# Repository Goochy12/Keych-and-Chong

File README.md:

# Keych and Chong
 Keyboard Designs

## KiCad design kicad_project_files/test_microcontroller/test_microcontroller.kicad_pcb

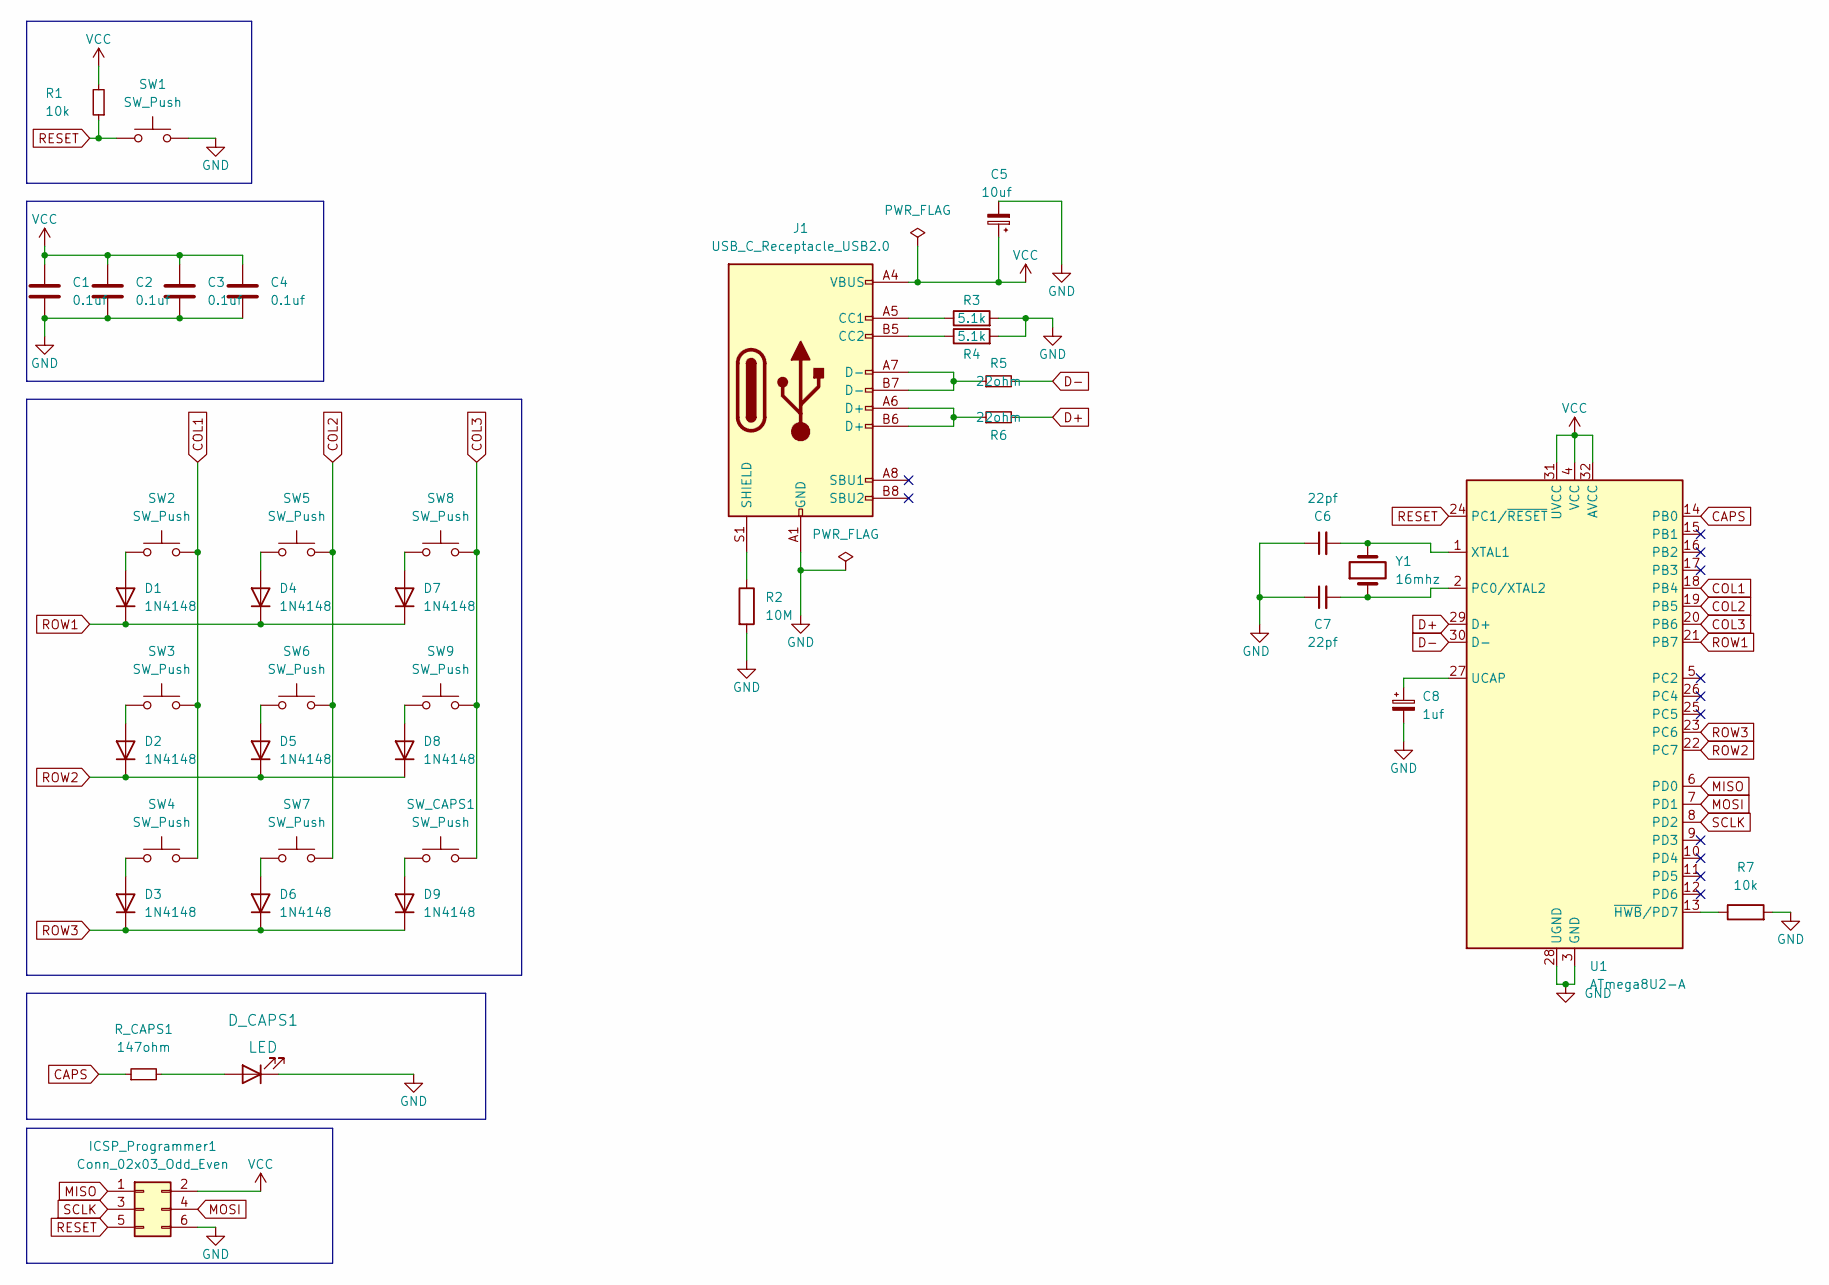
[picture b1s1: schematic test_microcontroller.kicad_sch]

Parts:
C1, C2, C3, C4: 0.1uf; C_Rect_L7.0mm_W2.0mm_P5.00mm
C5: 10uf; CP_Radial_D4.0mm_P1.50mm
C6, C7: 22pf; C_Disc_D3.0mm_W1.6mm_P2.50mm
C8: 1uf; CP_Radial_D4.0mm_P1.50mm
D1, D2, D3, D4, D5, D6, D7, D8, D9: 1N4148; D_DO-35_SOD27_P7.62mm_Horizontal
D_CAPS1: LED; LED_D3.0mm
ICSP_Programmer1: Conn_02x03_Odd_Even; PinHeader_2x03_P2.54mm_Vertical
J1: USB_C_Receptacle_USB2.0; USB_C_Receptacle_HRO_TYPE-C-31-M-12
R1, R7: 10k; R_Axial_DIN0204_L3.6mm_D1.6mm_P7.62mm_Horizontal
R2: 10M; R_Axial_DIN0204_L3.6mm_D1.6mm_P7.62mm_Horizontal
R3, R4: 5.1k; R_Axial_DIN0204_L3.6mm_D1.6mm_P7.62mm_Horizontal
R5, R6: 22ohm; R_Axial_DIN0204_L3.6mm_D1.6mm_P7.62mm_Horizontal
R_CAPS1: 147ohm; R_Axial_DIN0204_L3.6mm_D1.6mm_P7.62mm_Horizontal
SW1, SW2, SW3, SW4, SW5, SW6, SW7, SW8, SW9: SW_Push; SW_4-1437565-0
SW_CAPS1: SW_Push; SW_4-1437565-0
U1: ATmega8U2-A; TQFP-32_7x7mm_P0.8mm
Y1: 16mhz; Crystal_SMD_HC49-SD_HandSoldering

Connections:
CAPS: R_CAPS1.1, U1.14 (PB0)
COL1: SW2.2, SW3.2, SW4.2, U1.18 (PB4)
COL2: SW5.2, SW6.2, SW7.2, U1.19 (PB5)
COL3: SW8.2, SW9.2, SW_CAPS1.2, U1.20 (PB6)
D+: R6.2, U1.29 (D+)
D-: R5.2, U1.30 (D-)
GND: C1.2, C2.2, C3.2, C4.2, C5.2, C6.1, C7.1, C8.2, D_CAPS1.1 (K), ICSP_Programmer1.6, J1.A1 (GND), J1.A12 (GND), J1.B1 (GND), J1.B12 (GND), R2.2, R3.2, R4.2, R7.2, SW1.2, U1.3 (GND), U1.28 (UGND)
MISO: ICSP_Programmer1.1, U1.6 (PD0)
MOSI: ICSP_Programmer1.4, U1.7 (PD1)
unnamed: C6.2, U1.1 (XTAL1), Y1.2
unnamed: C7.2, U1.2 (PC0/XTAL2), Y1.1
unnamed: C8.1, U1.27 (UCAP)
unnamed: D1.2 (A), SW2.1
unnamed: D2.2 (A), SW3.1
unnamed: D3.2 (A), SW4.1
unnamed: D4.2 (A), SW5.1
unnamed: D5.2 (A), SW6.1
unnamed: D6.2 (A), SW7.1
unnamed: D7.2 (A), SW8.1
unnamed: D8.2 (A), SW9.1
unnamed: D9.2 (A), SW_CAPS1.1
unnamed: J1.A5 (CC1), R3.1
unnamed: J1.A6 (D+), J1.B6 (D+), R6.1
unnamed: J1.A7 (D-), J1.B7 (D-), R5.1
unnamed: J1.B5 (CC2), R4.1
unnamed: J1.S1 (SHIELD), R2.1
unnamed: R7.1, U1.13 (~HWB/PD7)
unnamed: D_CAPS1.2 (A), R_CAPS1.2
RESET: ICSP_Programmer1.5, R1.1, SW1.1, U1.24 (PC1/~RESET)
ROW1: D1.1 (K), D4.1 (K), D7.1 (K), U1.21 (PB7)
ROW2: D2.1 (K), D5.1 (K), D8.1 (K), U1.22 (PC7)
ROW3: D3.1 (K), D6.1 (K), D9.1 (K), U1.23 (PC6)
SCLK: ICSP_Programmer1.3, U1.8 (PD2)
VCC: C1.1, C2.1, C3.1, C4.1, C5.1, ICSP_Programmer1.2, J1.A4 (VBUS), J1.A9 (VBUS), J1.B4 (VBUS), J1.B9 (VBUS), R1.2, U1.4 (VCC), U1.31 (UVCC), U1.32 (AVCC)

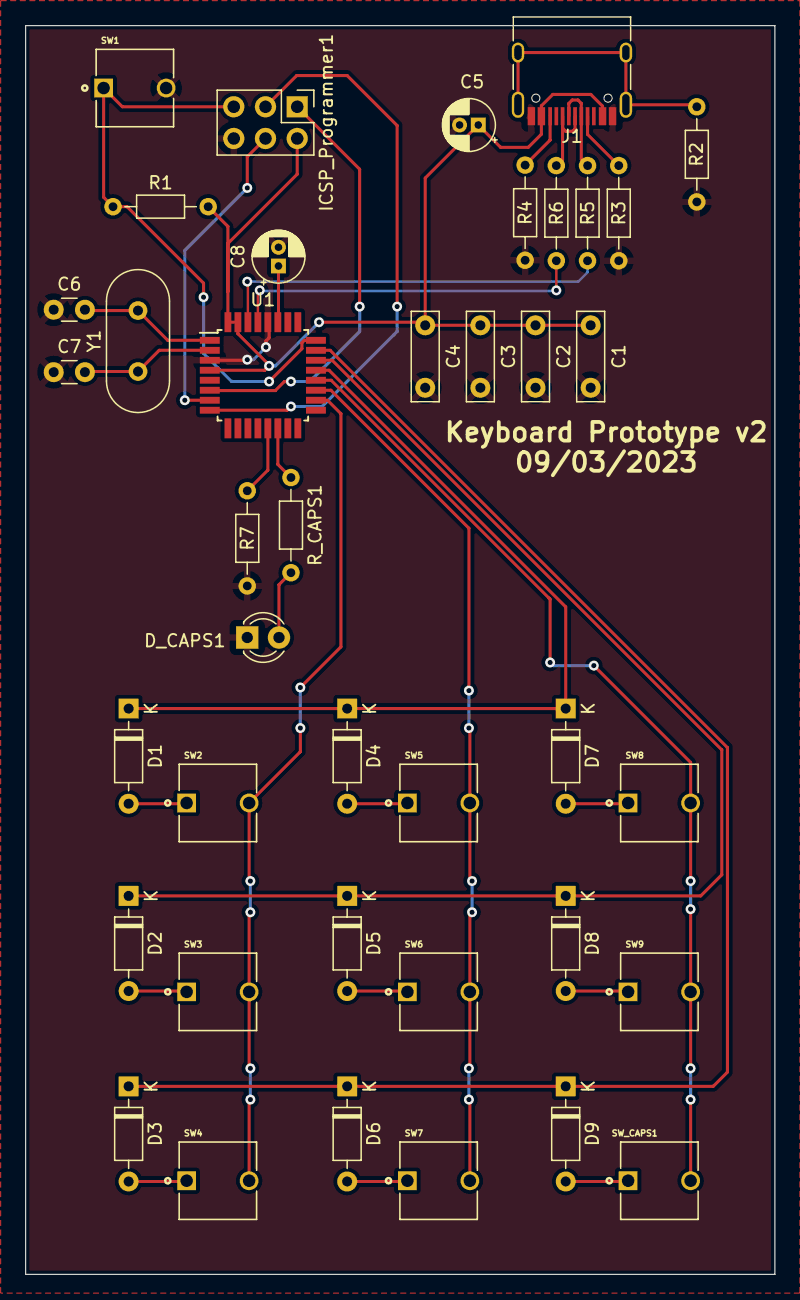
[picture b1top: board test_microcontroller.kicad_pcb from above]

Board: 2 copper layers, 60.0 x 100.0 mm, 40 parts (0 on the bottom side), 34 nets.

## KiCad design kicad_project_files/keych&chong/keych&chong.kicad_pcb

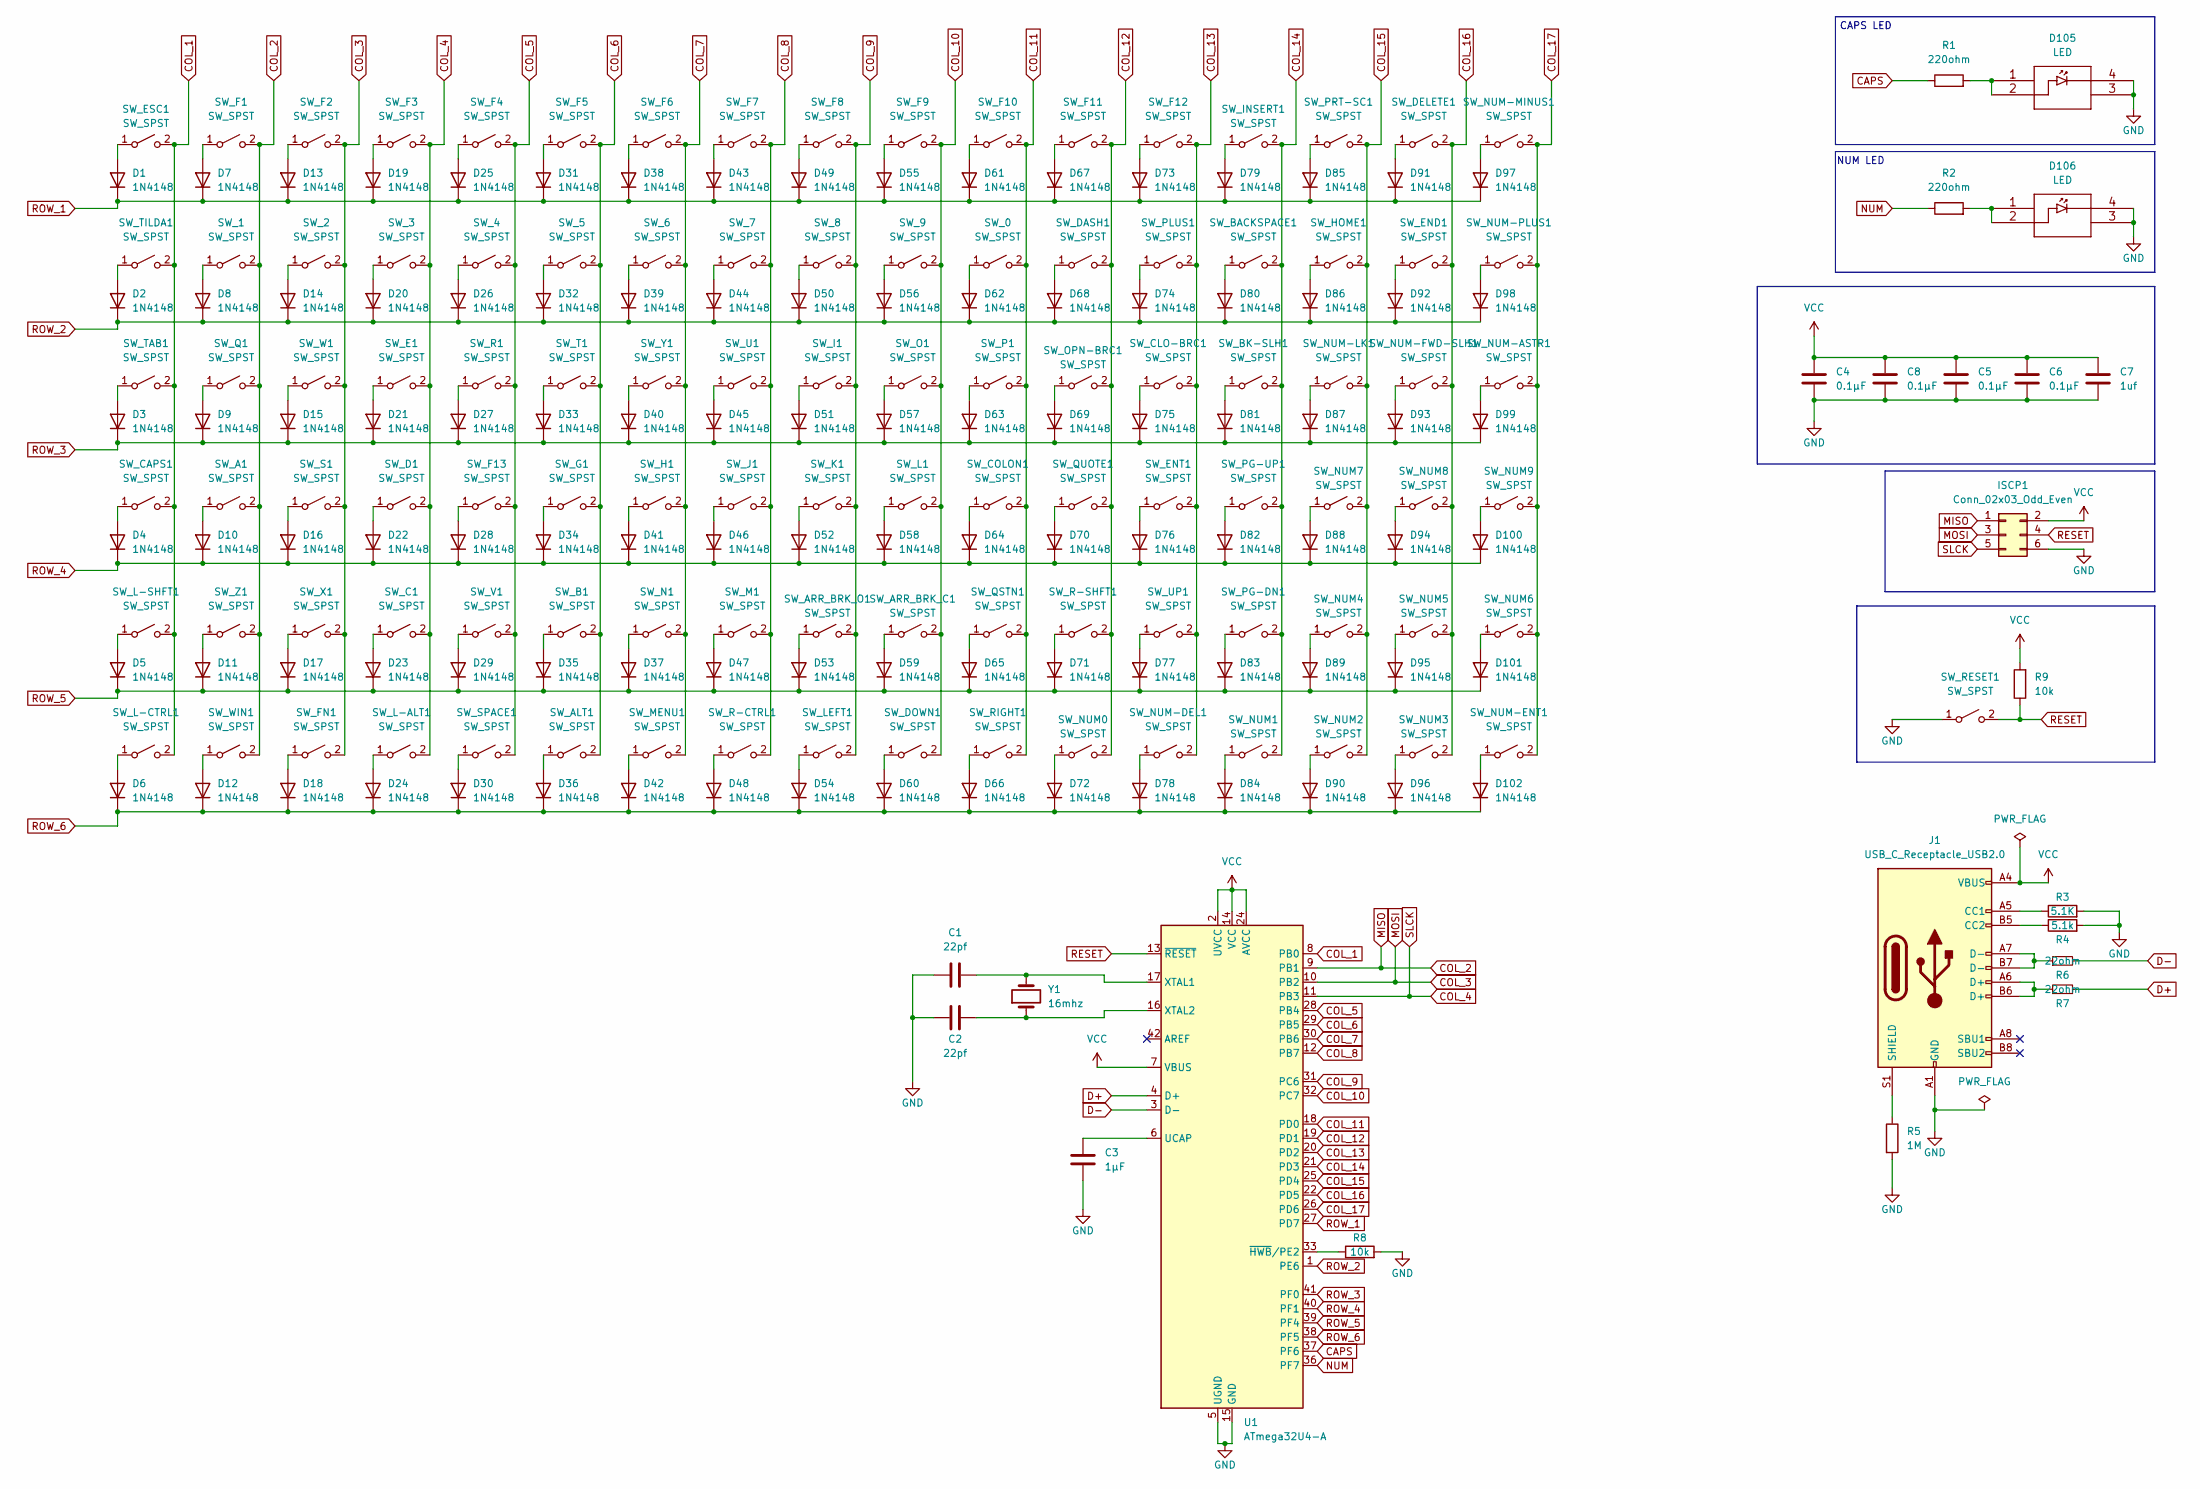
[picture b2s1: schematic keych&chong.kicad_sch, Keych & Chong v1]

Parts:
C1, C2: 22pf; C_1206_3216Metric_Pad1.33x1.80mm_HandSolder
C3: 1µF; C_1206_3216Metric_Pad1.33x1.80mm_HandSolder
C4, C5, C6, C8: 0.1µF; C_1206_3216Metric_Pad1.33x1.80mm_HandSolder
C7: 1uf; C_1206_3216Metric_Pad1.33x1.80mm_HandSolder
D1, D2, D3, D4, D5, D6, D7, D8, D9, D10, D11, D12, D13, D14, D15, D16, D17, D18, D19, D20, D21, D22, D23, D24, D25, D26, D27, D28, D29, D30, D31, D32, D33, D34, D35, D36, D37, D38, D39, D40, D41, D42, D43, D44, D45, D46, D47, D48, D49, D50, D51, D52, D53, D54, D55, D56, D57, D58, D59, D60, D61, D62, D63, D64, D65, D66, D67, D68, D69, D70, D71, D72, D73, D74, D75, D76, D77, D78, D79, D80, D81, D82, D83, D84, D85, D86, D87, D88, D89, D90, D91, D92, D93, D94, D95, D96, D97, D98, D99, D100, D101, D102: 1N4148; D_SOD-123
D105, D106: LED; CLA1A-WKW-CXAYB153
ISCP1: Conn_02x03_Odd_Even; PinHeader_2x03_P2.00mm_Vertical
J1: USB_C_Receptacle_USB2.0; USB_C_Receptacle_HRO_TYPE-C-31-M-12
R1, R2: 220ohm; R_0402_1005Metric_Pad0.72x0.64mm_HandSolder
R3: 5.1K; R_1206_3216Metric_Pad1.30x1.75mm_HandSolder
R4: 5.1k; R_1206_3216Metric_Pad1.30x1.75mm_HandSolder
R5: 1M; R_1206_3216Metric_Pad1.30x1.75mm_HandSolder
R6, R7: 22ohm; R_1206_3216Metric_Pad1.30x1.75mm_HandSolder
R8, R9: 10k; R_1206_3216Metric_Pad1.30x1.75mm_HandSolder
SW_0, SW_1, SW_2, SW_3, SW_4, SW_5, SW_6, SW_7, SW_8, SW_9: SW_SPST; SW_Cherry_MX_1.00u_Plate
SW_A1: SW_SPST; SW_Cherry_MX_1.00u_Plate
SW_ALT1: SW_SPST; SW_Cherry_MX_1.00u_Plate
SW_ARR_BRK_C1: SW_SPST; SW_Cherry_MX_1.00u_Plate
SW_ARR_BRK_O1: SW_SPST; SW_Cherry_MX_1.00u_Plate
SW_B1: SW_SPST; SW_Cherry_MX_1.00u_Plate
SW_BACKSPACE1: SW_SPST; SW_Cherry_MX_1.00u_Plate
SW_BK-SLH1: SW_SPST; SW_Cherry_MX_1.00u_Plate
SW_C1: SW_SPST; SW_Cherry_MX_1.00u_Plate
SW_CAPS1: SW_SPST; SW_Cherry_MX_1.00u_Plate
SW_CLO-BRC1: SW_SPST; SW_Cherry_MX_1.00u_Plate
SW_COLON1: SW_SPST; SW_Cherry_MX_1.00u_Plate
SW_D1: SW_SPST; SW_Cherry_MX_1.00u_Plate
SW_DASH1: SW_SPST; SW_Cherry_MX_1.00u_Plate
SW_DELETE1: SW_SPST; SW_Cherry_MX_1.00u_Plate
SW_DOWN1: SW_SPST; SW_Cherry_MX_1.00u_Plate
SW_E1: SW_SPST; SW_Cherry_MX_1.00u_Plate
SW_END1: SW_SPST; SW_Cherry_MX_1.00u_Plate
SW_ENT1: SW_SPST; SW_Cherry_MX_1.00u_Plate
SW_ESC1: SW_SPST; SW_Cherry_MX_1.00u_Plate
SW_F1, SW_F2, SW_F3, SW_F4, SW_F5, SW_F6, SW_F7, SW_F8, SW_F9, SW_F10, SW_F11, SW_F12, SW_F13: SW_SPST; SW_Cherry_MX_1.00u_Plate
SW_FN1: SW_SPST; SW_Cherry_MX_1.00u_Plate
SW_G1: SW_SPST; SW_Cherry_MX_1.00u_Plate
SW_H1: SW_SPST; SW_Cherry_MX_1.00u_Plate
SW_HOME1: SW_SPST; SW_Cherry_MX_1.00u_Plate
SW_I1: SW_SPST; SW_Cherry_MX_1.00u_Plate
SW_INSERT1: SW_SPST; SW_Cherry_MX_1.00u_Plate
SW_J1: SW_SPST; SW_Cherry_MX_1.00u_Plate
SW_K1: SW_SPST; SW_Cherry_MX_1.00u_Plate
SW_L1: SW_SPST; SW_Cherry_MX_1.00u_Plate
SW_L-ALT1: SW_SPST; SW_Cherry_MX_1.00u_Plate
SW_L-CTRL1: SW_SPST; SW_Cherry_MX_1.00u_Plate
SW_L-SHFT1: SW_SPST; SW_Cherry_MX_1.00u_Plate
SW_LEFT1: SW_SPST; SW_Cherry_MX_1.00u_Plate
SW_M1: SW_SPST; SW_Cherry_MX_1.00u_Plate
SW_MENU1: SW_SPST; SW_Cherry_MX_1.00u_Plate
SW_N1: SW_SPST; SW_Cherry_MX_1.00u_Plate
SW_NUM0, SW_NUM1, SW_NUM2, SW_NUM3, SW_NUM4, SW_NUM5, SW_NUM6, SW_NUM7, SW_NUM8, SW_NUM9: SW_SPST; SW_Cherry_MX_1.00u_Plate
SW_NUM-ASTR1: SW_SPST; SW_Cherry_MX_1.00u_Plate
SW_NUM-DEL1: SW_SPST; SW_Cherry_MX_1.00u_Plate
SW_NUM-ENT1: SW_SPST; SW_Cherry_MX_1.00u_Plate
SW_NUM-FWD-SLH1: SW_SPST; SW_Cherry_MX_1.00u_Plate
SW_NUM-LK1: SW_SPST; SW_Cherry_MX_1.00u_Plate
SW_NUM-MINUS1: SW_SPST; SW_Cherry_MX_1.00u_Plate
SW_NUM-PLUS1: SW_SPST; SW_Cherry_MX_1.00u_Plate
SW_O1: SW_SPST; SW_Cherry_MX_1.00u_Plate
SW_OPN-BRC1: SW_SPST; SW_Cherry_MX_1.00u_Plate
SW_P1: SW_SPST; SW_Cherry_MX_1.00u_Plate
SW_PG-DN1: SW_SPST; SW_Cherry_MX_1.00u_Plate
SW_PG-UP1: SW_SPST; SW_Cherry_MX_1.00u_Plate
SW_PLUS1: SW_SPST; SW_Cherry_MX_1.00u_Plate
SW_PRT-SC1: SW_SPST; SW_Cherry_MX_1.00u_Plate
SW_Q1: SW_SPST; SW_Cherry_MX_1.00u_Plate
SW_QSTN1: SW_SPST; SW_Cherry_MX_1.00u_Plate
SW_QUOTE1: SW_SPST; SW_Cherry_MX_1.00u_Plate
SW_R1: SW_SPST; SW_Cherry_MX_1.00u_Plate
SW_R-CTRL1: SW_SPST; SW_Cherry_MX_1.00u_Plate
SW_R-SHFT1: SW_SPST; SW_Cherry_MX_1.00u_Plate
SW_RESET1: SW_SPST; SW_4-1437565-0
SW_RIGHT1: SW_SPST; SW_Cherry_MX_1.00u_Plate
SW_S1: SW_SPST; SW_Cherry_MX_1.00u_Plate
SW_SPACE1: SW_SPST; SW_Cherry_MX_1.00u_Plate
SW_T1: SW_SPST; SW_Cherry_MX_1.00u_Plate
SW_TAB1: SW_SPST; SW_Cherry_MX_1.00u_Plate
SW_TILDA1: SW_SPST; SW_Cherry_MX_1.00u_Plate
SW_U1: SW_SPST; SW_Cherry_MX_1.00u_Plate
SW_UP1: SW_SPST; SW_Cherry_MX_1.00u_Plate
SW_V1: SW_SPST; SW_Cherry_MX_1.00u_Plate
SW_W1: SW_SPST; SW_Cherry_MX_1.00u_Plate
SW_WIN1: SW_SPST; SW_Cherry_MX_1.00u_Plate
SW_X1: SW_SPST; SW_Cherry_MX_1.00u_Plate
SW_Y1: SW_SPST; SW_Cherry_MX_1.00u_Plate
SW_Z1: SW_SPST; SW_Cherry_MX_1.00u_Plate
U1: ATmega32U4-A; ATMEGA32U4RC-AU
Y1: 16mhz; Crystal_HC49-4H_Vertical

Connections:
CAPS: R1.1, U1.37 (PF6)
COL_1: SW_CAPS1.2 (B), SW_ESC1.2 (B), SW_L-CTRL1.2 (B), SW_L-SHFT1.2 (B), SW_TAB1.2 (B), SW_TILDA1.2 (B), U1.8 (PB0)
COL_2: ISCP1.1, SW_1.2 (B), SW_A1.2 (B), SW_F1.2 (B), SW_Q1.2 (B), SW_WIN1.2 (B), SW_Z1.2 (B), U1.9 (PB1)
COL_3: ISCP1.3, SW_2.2 (B), SW_F2.2 (B), SW_FN1.2 (B), SW_S1.2 (B), SW_W1.2 (B), SW_X1.2 (B), U1.10 (PB2)
COL_4: ISCP1.5, SW_3.2 (B), SW_C1.2 (B), SW_D1.2 (B), SW_E1.2 (B), SW_F3.2 (B), SW_L-ALT1.2 (B), U1.11 (PB3)
COL_5: SW_4.2 (B), SW_F4.2 (B), SW_F13.2 (B), SW_R1.2 (B), SW_SPACE1.2 (B), SW_V1.2 (B), U1.28 (PB4)
COL_6: SW_5.2 (B), SW_ALT1.2 (B), SW_B1.2 (B), SW_F5.2 (B), SW_G1.2 (B), SW_T1.2 (B), U1.29 (PB5)
COL_7: SW_6.2 (B), SW_F6.2 (B), SW_H1.2 (B), SW_MENU1.2 (B), SW_N1.2 (B), SW_Y1.2 (B), U1.30 (PB6)
COL_8: SW_7.2 (B), SW_F7.2 (B), SW_J1.2 (B), SW_M1.2 (B), SW_R-CTRL1.2 (B), SW_U1.2 (B), U1.12 (PB7)
COL_9: SW_8.2 (B), SW_ARR_BRK_O1.2 (B), SW_F8.2 (B), SW_I1.2 (B), SW_K1.2 (B), SW_LEFT1.2 (B), U1.31 (PC6)
COL_10: SW_9.2 (B), SW_ARR_BRK_C1.2 (B), SW_DOWN1.2 (B), SW_F9.2 (B), SW_L1.2 (B), SW_O1.2 (B), U1.32 (PC7)
COL_11: SW_0.2 (B), SW_COLON1.2 (B), SW_F10.2 (B), SW_P1.2 (B), SW_QSTN1.2 (B), SW_RIGHT1.2 (B), U1.18 (PD0)
COL_12: SW_DASH1.2 (B), SW_F11.2 (B), SW_NUM0.2 (B), SW_OPN-BRC1.2 (B), SW_QUOTE1.2 (B), SW_R-SHFT1.2 (B), U1.19 (PD1)
COL_13: SW_CLO-BRC1.2 (B), SW_ENT1.2 (B), SW_F12.2 (B), SW_NUM-DEL1.2 (B), SW_PLUS1.2 (B), SW_UP1.2 (B), U1.20 (PD2)
COL_14: SW_BACKSPACE1.2 (B), SW_BK-SLH1.2 (B), SW_INSERT1.2 (B), SW_NUM1.2 (B), SW_PG-DN1.2 (B), SW_PG-UP1.2 (B), U1.21 (PD3)
COL_15: SW_HOME1.2 (B), SW_NUM2.2 (B), SW_NUM4.2 (B), SW_NUM7.2 (B), SW_NUM-LK1.2 (B), SW_PRT-SC1.2 (B), U1.25 (PD4)
COL_16: SW_DELETE1.2 (B), SW_END1.2 (B), SW_NUM3.2 (B), SW_NUM5.2 (B), SW_NUM8.2 (B), SW_NUM-FWD-SLH1.2 (B), U1.22 (PD5)
COL_17: SW_NUM6.2 (B), SW_NUM9.2 (B), SW_NUM-ASTR1.2 (B), SW_NUM-ENT1.2 (B), SW_NUM-MINUS1.2 (B), SW_NUM-PLUS1.2 (B), U1.26 (PD6)
D+: R7.2, U1.4 (D+)
D-: R6.2, U1.3 (D-)
GND: C1.1, C2.1, C3.2, C4.2, C5.2, C6.2, C7.2, C8.2, D105.3, D105.4, D106.3, D106.4, ISCP1.6, J1.A1 (GND), J1.A12 (GND), J1.B1 (GND), J1.B12 (GND), R3.2, R4.2, R5.2, R8.2, SW_RESET1.1 (A), U1.5 (UGND), U1.15 (GND), U1.23 (GND), U1.35 (GND), U1.43 (GND)
NUM: R2.1, U1.36 (PF7)
unnamed: C1.2, U1.17 (XTAL1), Y1.2
unnamed: C2.2, U1.16 (XTAL2), Y1.1
unnamed: C3.1, U1.6 (UCAP)
unnamed: D1.2 (A), SW_ESC1.1 (A)
unnamed: D2.2 (A), SW_TILDA1.1 (A)
unnamed: D3.2 (A), SW_TAB1.1 (A)
unnamed: D4.2 (A), SW_CAPS1.1 (A)
unnamed: D5.2 (A), SW_L-SHFT1.1 (A)
unnamed: D6.2 (A), SW_L-CTRL1.1 (A)
unnamed: D7.2 (A), SW_F1.1 (A)
unnamed: D8.2 (A), SW_1.1 (A)
unnamed: D9.2 (A), SW_Q1.1 (A)
unnamed: D10.2 (A), SW_A1.1 (A)
unnamed: D11.2 (A), SW_Z1.1 (A)
unnamed: D12.2 (A), SW_WIN1.1 (A)
unnamed: D13.2 (A), SW_F2.1 (A)
unnamed: D14.2 (A), SW_2.1 (A)
unnamed: D15.2 (A), SW_W1.1 (A)
unnamed: D16.2 (A), SW_S1.1 (A)
unnamed: D17.2 (A), SW_X1.1 (A)
unnamed: D18.2 (A), SW_FN1.1 (A)
unnamed: D19.2 (A), SW_F3.1 (A)
unnamed: D20.2 (A), SW_3.1 (A)
unnamed: D21.2 (A), SW_E1.1 (A)
unnamed: D22.2 (A), SW_D1.1 (A)
unnamed: D23.2 (A), SW_C1.1 (A)
unnamed: D24.2 (A), SW_L-ALT1.1 (A)
unnamed: D25.2 (A), SW_F4.1 (A)
unnamed: D26.2 (A), SW_4.1 (A)
unnamed: D27.2 (A), SW_R1.1 (A)
unnamed: D28.2 (A), SW_F13.1 (A)
unnamed: D29.2 (A), SW_V1.1 (A)
unnamed: D30.2 (A), SW_SPACE1.1 (A)
unnamed: D31.2 (A), SW_F5.1 (A)
unnamed: D32.2 (A), SW_5.1 (A)
unnamed: D33.2 (A), SW_T1.1 (A)
unnamed: D34.2 (A), SW_G1.1 (A)
unnamed: D35.2 (A), SW_B1.1 (A)
unnamed: D36.2 (A), SW_ALT1.1 (A)
unnamed: D37.2 (A), SW_N1.1 (A)
unnamed: D38.2 (A), SW_F6.1 (A)
unnamed: D39.2 (A), SW_6.1 (A)
unnamed: D40.2 (A), SW_Y1.1 (A)
unnamed: D41.2 (A), SW_H1.1 (A)
unnamed: D42.2 (A), SW_MENU1.1 (A)
unnamed: D43.2 (A), SW_F7.1 (A)
unnamed: D44.2 (A), SW_7.1 (A)
unnamed: D45.2 (A), SW_U1.1 (A)
unnamed: D46.2 (A), SW_J1.1 (A)
unnamed: D47.2 (A), SW_M1.1 (A)
unnamed: D48.2 (A), SW_R-CTRL1.1 (A)
unnamed: D49.2 (A), SW_F8.1 (A)
unnamed: D50.2 (A), SW_8.1 (A)
unnamed: D51.2 (A), SW_I1.1 (A)
unnamed: D52.2 (A), SW_K1.1 (A)
unnamed: D53.2 (A), SW_ARR_BRK_O1.1 (A)
unnamed: D54.2 (A), SW_LEFT1.1 (A)
unnamed: D55.2 (A), SW_F9.1 (A)
unnamed: D56.2 (A), SW_9.1 (A)
unnamed: D57.2 (A), SW_O1.1 (A)
unnamed: D58.2 (A), SW_L1.1 (A)
unnamed: D59.2 (A), SW_ARR_BRK_C1.1 (A)
unnamed: D60.2 (A), SW_DOWN1.1 (A)
unnamed: D61.2 (A), SW_F10.1 (A)
unnamed: D62.2 (A), SW_0.1 (A)
unnamed: D63.2 (A), SW_P1.1 (A)
unnamed: D64.2 (A), SW_COLON1.1 (A)
unnamed: D65.2 (A), SW_QSTN1.1 (A)
unnamed: D66.2 (A), SW_RIGHT1.1 (A)
unnamed: D67.2 (A), SW_F11.1 (A)
unnamed: D68.2 (A), SW_DASH1.1 (A)
unnamed: D69.2 (A), SW_OPN-BRC1.1 (A)
unnamed: D70.2 (A), SW_QUOTE1.1 (A)
unnamed: D71.2 (A), SW_R-SHFT1.1 (A)
unnamed: D72.2 (A), SW_NUM0.1 (A)
unnamed: D73.2 (A), SW_F12.1 (A)
unnamed: D74.2 (A), SW_PLUS1.1 (A)
unnamed: D75.2 (A), SW_CLO-BRC1.1 (A)
unnamed: D76.2 (A), SW_ENT1.1 (A)
unnamed: D77.2 (A), SW_UP1.1 (A)
unnamed: D78.2 (A), SW_NUM-DEL1.1 (A)
unnamed: D79.2 (A), SW_INSERT1.1 (A)
unnamed: D80.2 (A), SW_BACKSPACE1.1 (A)
unnamed: D81.2 (A), SW_BK-SLH1.1 (A)
unnamed: D82.2 (A), SW_PG-UP1.1 (A)
unnamed: D83.2 (A), SW_PG-DN1.1 (A)
unnamed: D84.2 (A), SW_NUM1.1 (A)
unnamed: D85.2 (A), SW_PRT-SC1.1 (A)
unnamed: D86.2 (A), SW_HOME1.1 (A)
unnamed: D87.2 (A), SW_NUM-LK1.1 (A)
unnamed: D88.2 (A), SW_NUM7.1 (A)
unnamed: D89.2 (A), SW_NUM4.1 (A)
unnamed: D90.2 (A), SW_NUM2.1 (A)
unnamed: D91.2 (A), SW_DELETE1.1 (A)
unnamed: D92.2 (A), SW_END1.1 (A)
unnamed: D93.2 (A), SW_NUM-FWD-SLH1.1 (A)
unnamed: D94.2 (A), SW_NUM8.1 (A)
unnamed: D95.2 (A), SW_NUM5.1 (A)
unnamed: D96.2 (A), SW_NUM3.1 (A)
unnamed: D97.2 (A), SW_NUM-MINUS1.1 (A)
unnamed: D98.2 (A), SW_NUM-PLUS1.1 (A)
unnamed: D99.2 (A), SW_NUM-ASTR1.1 (A)
unnamed: D100.2 (A), SW_NUM9.1 (A)
unnamed: D101.2 (A), SW_NUM6.1 (A)
unnamed: D102.2 (A), SW_NUM-ENT1.1 (A)
unnamed: D105.1, D105.2, R1.2
unnamed: D106.1, D106.2, R2.2
unnamed: J1.A5 (CC1), R3.1
unnamed: J1.A6 (D+), J1.B6 (D+), R7.1
unnamed: J1.A7 (D-), J1.B7 (D-), R6.1
unnamed: J1.B5 (CC2), R4.1
unnamed: J1.S1 (SHIELD), R5.1
unnamed: R8.1, U1.33 (~HWB/PE2)
RESET: ISCP1.4, R9.1, SW_RESET1.2 (B), U1.13 (~RESET)
ROW_1: D1.1 (K), D7.1 (K), D13.1 (K), D19.1 (K), D25.1 (K), D31.1 (K), D38.1 (K), D43.1 (K), D49.1 (K), D55.1 (K), D61.1 (K), D67.1 (K), D73.1 (K), D79.1 (K), D85.1 (K), D91.1 (K), D97.1 (K), U1.27 (PD7)
ROW_2: D2.1 (K), D8.1 (K), D14.1 (K), D20.1 (K), D26.1 (K), D32.1 (K), D39.1 (K), D44.1 (K), D50.1 (K), D56.1 (K), D62.1 (K), D68.1 (K), D74.1 (K), D80.1 (K), D86.1 (K), D92.1 (K), D98.1 (K), U1.1 (PE6)
ROW_3: D3.1 (K), D9.1 (K), D15.1 (K), D21.1 (K), D27.1 (K), D33.1 (K), D40.1 (K), D45.1 (K), D51.1 (K), D57.1 (K), D63.1 (K), D69.1 (K), D75.1 (K), D81.1 (K), D87.1 (K), D93.1 (K), D99.1 (K), U1.41 (PF0)
ROW_4: D4.1 (K), D10.1 (K), D16.1 (K), D22.1 (K), D28.1 (K), D34.1 (K), D41.1 (K), D46.1 (K), D52.1 (K), D58.1 (K), D64.1 (K), D70.1 (K), D76.1 (K), D82.1 (K), D88.1 (K), D94.1 (K), D100.1 (K), U1.40 (PF1)
ROW_5: D5.1 (K), D11.1 (K), D17.1 (K), D23.1 (K), D29.1 (K), D35.1 (K), D37.1 (K), D47.1 (K), D53.1 (K), D59.1 (K), D65.1 (K), D71.1 (K), D77.1 (K), D83.1 (K), D89.1 (K), D95.1 (K), D101.1 (K), U1.39 (PF4)
ROW_6: D6.1 (K), D12.1 (K), D18.1 (K), D24.1 (K), D30.1 (K), D36.1 (K), D42.1 (K), D48.1 (K), D54.1 (K), D60.1 (K), D66.1 (K), D72.1 (K), D78.1 (K), D84.1 (K), D90.1 (K), D96.1 (K), D102.1 (K), U1.38 (PF5)
VCC: C4.1, C5.1, C6.1, C7.1, C8.1, ISCP1.2, J1.A4 (VBUS), J1.A9 (VBUS), J1.B4 (VBUS), J1.B9 (VBUS), R9.2, U1.2 (UVCC), U1.7 (VBUS), U1.14 (VCC), U1.24 (AVCC), U1.34 (VCC), U1.44 (AVCC)

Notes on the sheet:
NUM LED
CAPS LED

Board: 2 copper layers, 228 parts (0 on the bottom side), 143 nets, no tracks yet.

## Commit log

2022-06-02 add initial kicad project files
2022-06-03 add 104 buttons to schematic
2022-06-04 align matrix
2022-06-04 add connections to matrix schematic
2022-06-05 updated matrix and added external crystal to schematic
2022-06-05 add datasheet and design considerations
2022-06-05 add decoupling capacitors to VCC
2022-06-05 add usb c to schematic
2022-06-06 refactor folder structure and add test circuit
2022-06-08 add footprints to test scheme
2022-06-08 create pcb
2022-06-14 add ICSP
2022-06-14 add traces to pcb
2022-06-15 add pcb traces
2022-06-15 complete traces
2022-06-16 finish pcb and export
2022-06-18 connect schematic
2022-06-18 add diode to usb input voltage
2022-06-20 add diode to pcb
2022-06-21 remove diode
2022-06-21 Revert "add diode to pcb"
    This reverts commit 20722a3885263840da117607ee800e449ae5a56b.
2022-06-21 make tracks larger
2022-06-21 refactor pcb and export
2022-06-21 adjust usb c footprint
2022-06-22 add footprints
2022-06-25 create copy of test
2022-06-25 add new mcu and voltage regulator
2022-06-25 new voltage reg
2022-06-26 update to utmega8u2
2022-06-26 update schematic
2022-06-26 fix pcb
2022-06-26 export list
2022-08-06 make pcb smaller
2022-08-06 new BOM
2022-08-06 update usb symbol
2022-08-07 update pcb - new usb
2022-08-07 Revert "Merge branch 'main' of https://github.com/Goochy12/Keych-and-Chong"
    This reverts commit 89a84faf58301de3235cbf20de78d9bc04a2e137, reversing
    changes made to 8f87e55d37906a6161fcb491ec761d32a82a7e61.
2022-08-07 Revert "Create printing.pdf"
    This reverts commit 1ba304ad0df449a8c0a1200daa24c0f94e3b940c.
2022-08-07 Revert "Merge branch 'main' of https://github.com/Goochy12/Keych-and-Chong"
    This reverts commit 8f87e55d37906a6161fcb491ec761d32a82a7e61, reversing
    changes made to 1ba304ad0df449a8c0a1200daa24c0f94e3b940c.
2022-08-07 Revert "Merge branch 'main' of https://github.com/Goochy12/Keych-and-Chong"
    This reverts commit 16abbc7445c5651a73e155e9e96779087de1ba9e, reversing
    changes made to 1815a7fd47ddf9f2f8e947e23bdaa21c8c5a7216.
2022-08-07 Revert "Revert "Merge branch 'main' of https://github.com/Goochy12/Keych-and-Chong""
    This reverts commit c8ae18377c4835621f54e74df08cb33c8008ec0a.
2022-08-07 update pcb
2022-08-11 prof_pcb
2022-08-13 pcb v1
2022-08-13 create split keyboard project files
2022-08-14 create split keyboard - MCU + cap
2022-08-14 update rows and cols
2022-08-14 update footprints
2022-08-16 place keys on pcb
2022-08-17 add footprints and symbols
2022-08-17 place diodes
2022-08-18 align diodes
2022-09-19 add dev firmware
2022-11-05 create Test Microcontroller firmware package
2022-11-06 add lufa library to test micro firmware
2022-11-09 build
2022-11-13 fix callback descriptor
2022-11-13 clean
2022-11-13 fix bugs
2022-11-15 add pin definitions and keyboard matrix
2022-11-15 add simple scan matrix logic
2023-03-09 update Programming pin
2023-03-12 redesign icsp
2023-03-12 backup
2023-03-14 create gerber files
2023-03-14 add cad files
2023-03-14 create test atmega32u4
2023-03-14 update cad
2023-06-02 create project files
2023-06-03 complete wiring schematic
2023-06-03 assign footprints
2023-09-01 add test firmware
2023-09-04 add key presses to keyboard

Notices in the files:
parts and their libraries:
Copyright 2021 Accelerated Designs. All rights reserved.
